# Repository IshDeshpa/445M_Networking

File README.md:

# FreakyNetworking

**FreakyNetworking** is a lightweight, embedded networking stack designed to run on **FreakyRTOS**. It provides essential networking protocols and integrates with FreakyRTOS. This is also an example of how to integrate FreakyRTOS into a project using GNU-ARM. 

## 📄 Documentation

For detailed information about the implementation of the stack, please refer to the official documentation:

👉 [RTOS Networking Stack Documentation](https://ishdeshpa.com/blog/rtos-networking.html)

## Features
- MAC layer implementation
- IPv4 stack
- UDP transport
- DHCP client for dynamic IP configuration
- ARP request/reply handling
- ICMP ping utility
- TCP support (in development)
- RTOS integration for task scheduling and synchronization

## Supported Hardware
- TI `TM4C` microcontroller series
- Microchip WILC1000 WiFi module (SPI interface)
- There is a SPI breakout KiCad layout for the WILC1000 in the hw/ folder.

## Architecture & RTOS Integration
FreakyNetworking is tightly integrated with **FreakyRTOS**. It uses RTOS primitives such as tasks, semaphores, and timers to manage networking operations efficiently. 

The FreakyRTOS and FreakyNetworking are also integrated with **TivaWare** and **ValvanoWare**, enabling low-level hardware abstraction and peripheral management on TM4C devices.

## Toolchain
FreakyNetworking is built using the **GNU ARM Toolchain**, making it suitable for open-source and cross-platform development environments.

## Roadmap
- Complete TCP implementation with connection management
- TLS/SSL support
- IPv6 protocol support
- Advanced power management integration

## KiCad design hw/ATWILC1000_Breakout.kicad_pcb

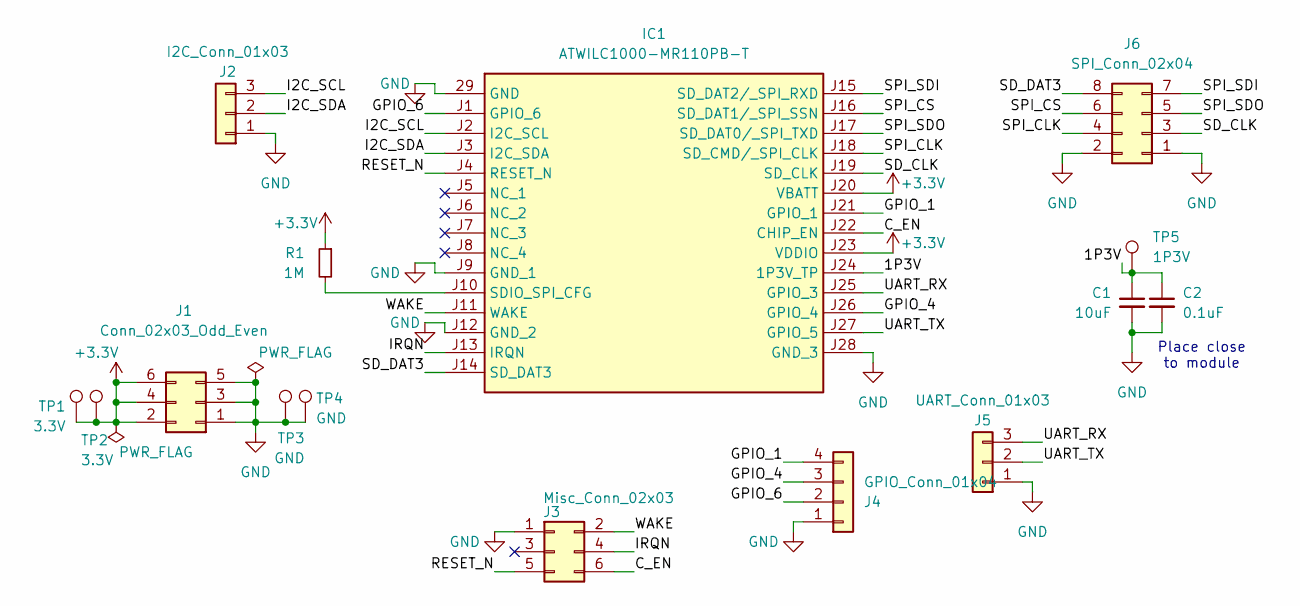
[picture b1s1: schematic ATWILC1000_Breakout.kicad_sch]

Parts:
C1: 10uF; C_0805_2012Metric_Pad1.18x1.45mm_HandSolder
C2: 0.1uF; C_0805_2012Metric_Pad1.18x1.45mm_HandSolder
IC1: ATWILC1000-MR110PB-T; ATWILC1000MR110PBT; Manufacturer_Part_Number ATWILC1000-MR110PB-T; Mouser Part Number 579-WILC1000MR110PBT
J1: Conn_02x03_Odd_Even; PinHeader_2x03_P2.54mm_Vertical
J2: I2C_Conn_01x03; PinHeader_1x03_P2.54mm_Vertical
J3: Misc_Conn_02x03; PinHeader_2x03_P2.54mm_Vertical
J4: GPIO_Conn_01x04; PinHeader_1x04_P2.54mm_Vertical
J5: UART_Conn_01x03; PinHeader_1x03_P2.54mm_Vertical
J6: SPI_Conn_02x04; PinHeader_2x04_P2.54mm_Vertical
R1: 1M; R_0805_2012Metric_Pad1.20x1.40mm_HandSolder
TP1, TP2: 3.3V; TestPoint_Plated_Hole_D3.0mm
TP3, TP4: GND; TestPoint_Plated_Hole_D3.0mm
TP5: 1P3V; TestPoint_Plated_Hole_D3.0mm

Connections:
+3.3V: IC1.J20 (VBATT), IC1.J23 (VDDIO), J1.2, J1.4, J1.6, R1.1, TP1.1, TP2.1
/1P3V: C1.1, C2.1, IC1.J24 (1P3V_TP), TP5.1
/C_EN: IC1.J22 (CHIP_EN), J3.6
/GPIO_1: IC1.J21 (GPIO_1), J4.4
/GPIO_4: IC1.J26 (GPIO_4), J4.3
/GPIO_6: IC1.J1 (GPIO_6), J4.2
/I2C_SCL: IC1.J2 (I2C_SCL), J2.3
/I2C_SDA: IC1.J3 (I2C_SDA), J2.2
/IRQN: IC1.J13 (IRQN), J3.4
/RESET_N: IC1.J4 (RESET_N), J3.5
/SD_CLK: IC1.J19 (SD_CLK), J6.3
/SD_DAT3: IC1.J14 (SD_DAT3), J6.8
/SPI_CLK: IC1.J18 (SD_CMD/_SPI_CLK), J6.4
/SPI_CS: IC1.J16 (SD_DAT1/_SPI_SSN), J6.6
/SPI_SDI: IC1.J15 (SD_DAT2/_SPI_RXD), J6.7
/SPI_SDO: IC1.J17 (SD_DAT0/_SPI_TXD), J6.5
/UART_RX: IC1.J25 (GPIO_3), J5.3
/UART_TX: IC1.J27 (GPIO_5), J5.2
/WAKE: IC1.J11 (WAKE), J3.2
GND: C1.2, C2.2, IC1.29 (GND), IC1.J9 (GND_1), IC1.J12 (GND_2), IC1.J28 (GND_3), J1.1, J1.3, J1.5, J2.1, J3.1, J4.1, J5.1, J6.1, J6.2, TP3.1, TP4.1
unnamed: IC1.J10 (SDIO_SPI_CFG), R1.2

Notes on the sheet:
Place close to module

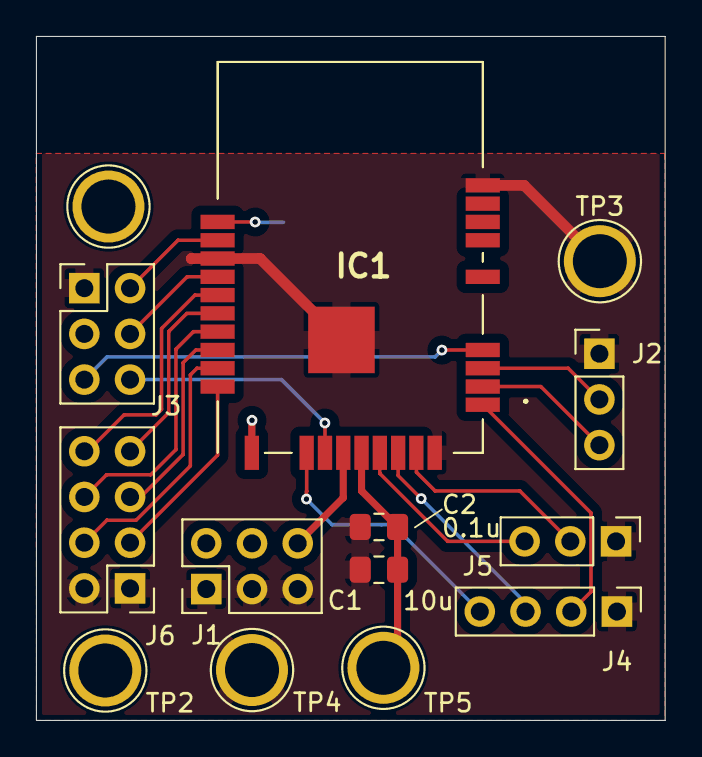
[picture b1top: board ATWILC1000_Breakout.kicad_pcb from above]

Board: 2 copper layers, 34.9 x 38.0 mm, 15 parts (1 on the bottom side), 21 nets.

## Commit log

2025-02-20 created initial schematic for WILC1000 and imported symbol
2025-02-20 imported CMakeLists
2025-02-20 started initial power setup for breakout board
2025-02-21 updated to the module rather than the chip
2025-02-22 blinky
2025-02-23 breakout layout first draft
2025-02-25 proposal
2025-02-25 small kicad modifications
2025-02-28 init riutal for the spi ports
2025-03-12 finished and ordered board
2025-03-14 bom and wilc firmware
2025-03-14 statup ritual
2025-03-31 added stuff
2025-03-31 driverlib added, testing basic spi transactions
2025-04-02 some firmware stuff idk rly know though
2025-04-05 stuff
2025-04-05 dir restructuring
2025-04-05 working ssi
2025-04-05 gitignore
2025-04-11 added gpio edge triggered interrupts
2025-04-12 switched to portE, added IRQ line
2025-04-12 finally fucking compiling holy fuck
2025-04-13 got further through the init ritual
2025-04-14 fucking shit who put gpt cod ein ehre
2025-04-14 spi is working on the correct ports now
2025-04-17 wilc
2025-04-17 move
2025-04-17 freakyrtos and makefile
2025-04-17 makefile 😭
2025-04-17 remove mz
2025-04-17 setting up conf file
2025-04-17 bus wrapper and bsp
2025-04-17 added falsh
2025-04-17 pushing
2025-04-17 bear
2025-04-17 remove deported
2025-04-17 spph
2025-04-17 stuf workin
2025-04-17 reading chip id
2025-04-17 linker fix
2025-04-17 trying bs
2025-04-17 got printf working
2025-04-17 exptions
2025-04-18 debgging pain
2025-04-18 debugging
2025-04-19 lisnting ssids
2025-04-19 networking thread
2025-04-19 memset and memcpy
2025-04-19 headers
2025-04-19 headers again
2025-04-19 semaphore oopsy
2025-04-19 thread stuf
2025-04-19 boutta refactor
2025-04-19 progress has been made
2025-04-21 working
2025-04-21 freaky bus
2025-04-22 ip files added
2025-04-22 started udp
2025-04-22 htos
2025-04-22 ip updates
2025-04-22 udp finish!
2025-04-23 fniished ip, not tested at all
2025-04-23 added testing code
2025-04-23 ip working
2025-04-23 somemore stuff
2025-04-23 covert funcs in glob
2025-04-23 build structure
2025-04-23 wokring on UDP
2025-04-23 moved files to src
2025-04-23 build system
2025-04-23 build system final
2025-04-23 ishan caoused a big merge conf
2025-04-23 hotfixes
2025-04-23 updated flashsign
2025-04-23 somethign simple
2025-04-23 reacreted th seg fuatl
2025-04-23 mac finsihed, not tested
2025-04-23 bah2
2025-04-24 made const size
2025-04-24 updated run.sh for compile eror rhcekcing
2025-04-24 added nano printf
2025-04-24 looking for the bug
2025-04-24 somehting
2025-04-24 got tx working now need to get rx working the script need to be made more adherant to our protocal
2025-04-25 started arp but not really
2025-04-25 rx now working although sort of unsure how
2025-04-25 icmp implemented; not yet tested
2025-04-25 started working on small ping application
2025-04-26 implemented a bunch of dhcp
2025-04-26 work
2025-04-27 mac fix
2025-04-27 freakt bis
2025-04-27 pushed
2025-04-27 good stuff
2025-04-28 more
2025-04-28 ishans about to shit the bed
2025-04-28 freaky busness
2025-04-28 freakiness
2025-04-28 freaky business
2025-04-28 merge
2025-04-28 ishan didnt use memcpy
2025-04-28 starting to prt
2025-04-28 dhcp routing
2025-04-28 aaaaaaaaa
2025-04-28 stuipd fix
2025-04-28 setting up for dhcp stuff
2025-04-28 shit
2025-04-28 finshed dhcp resp and offer peroceing
2025-04-28 tested ack
2025-04-28 baaah
2025-04-28 changed osmethign not snure waht
2025-04-28 fukcing stack size
2025-04-28 definitely getting somewhere
2025-04-28 sending dhcp
2025-04-28 logfile and stuff
2025-04-28 working somewhat
2025-04-28 support for bigger ihl, stil ignering the options
2025-04-28 fearky business
2025-04-28 updated logfile
2025-04-28 added checksum support for ihl > 5
2025-04-28 ping stuff
2025-04-29 ping
2025-04-29 freakybusiness
2025-04-29 support for arp rx
2025-04-29 wrote a user app and finsihed up arp
2025-04-29 logs
2025-04-29 mac tx
2025-04-29 arp support for mac
2025-04-29 arp working
2025-04-29 ping is wokring holy fuck
2025-04-29 wokring on udp rx
2025-05-09 readme and doumentation
